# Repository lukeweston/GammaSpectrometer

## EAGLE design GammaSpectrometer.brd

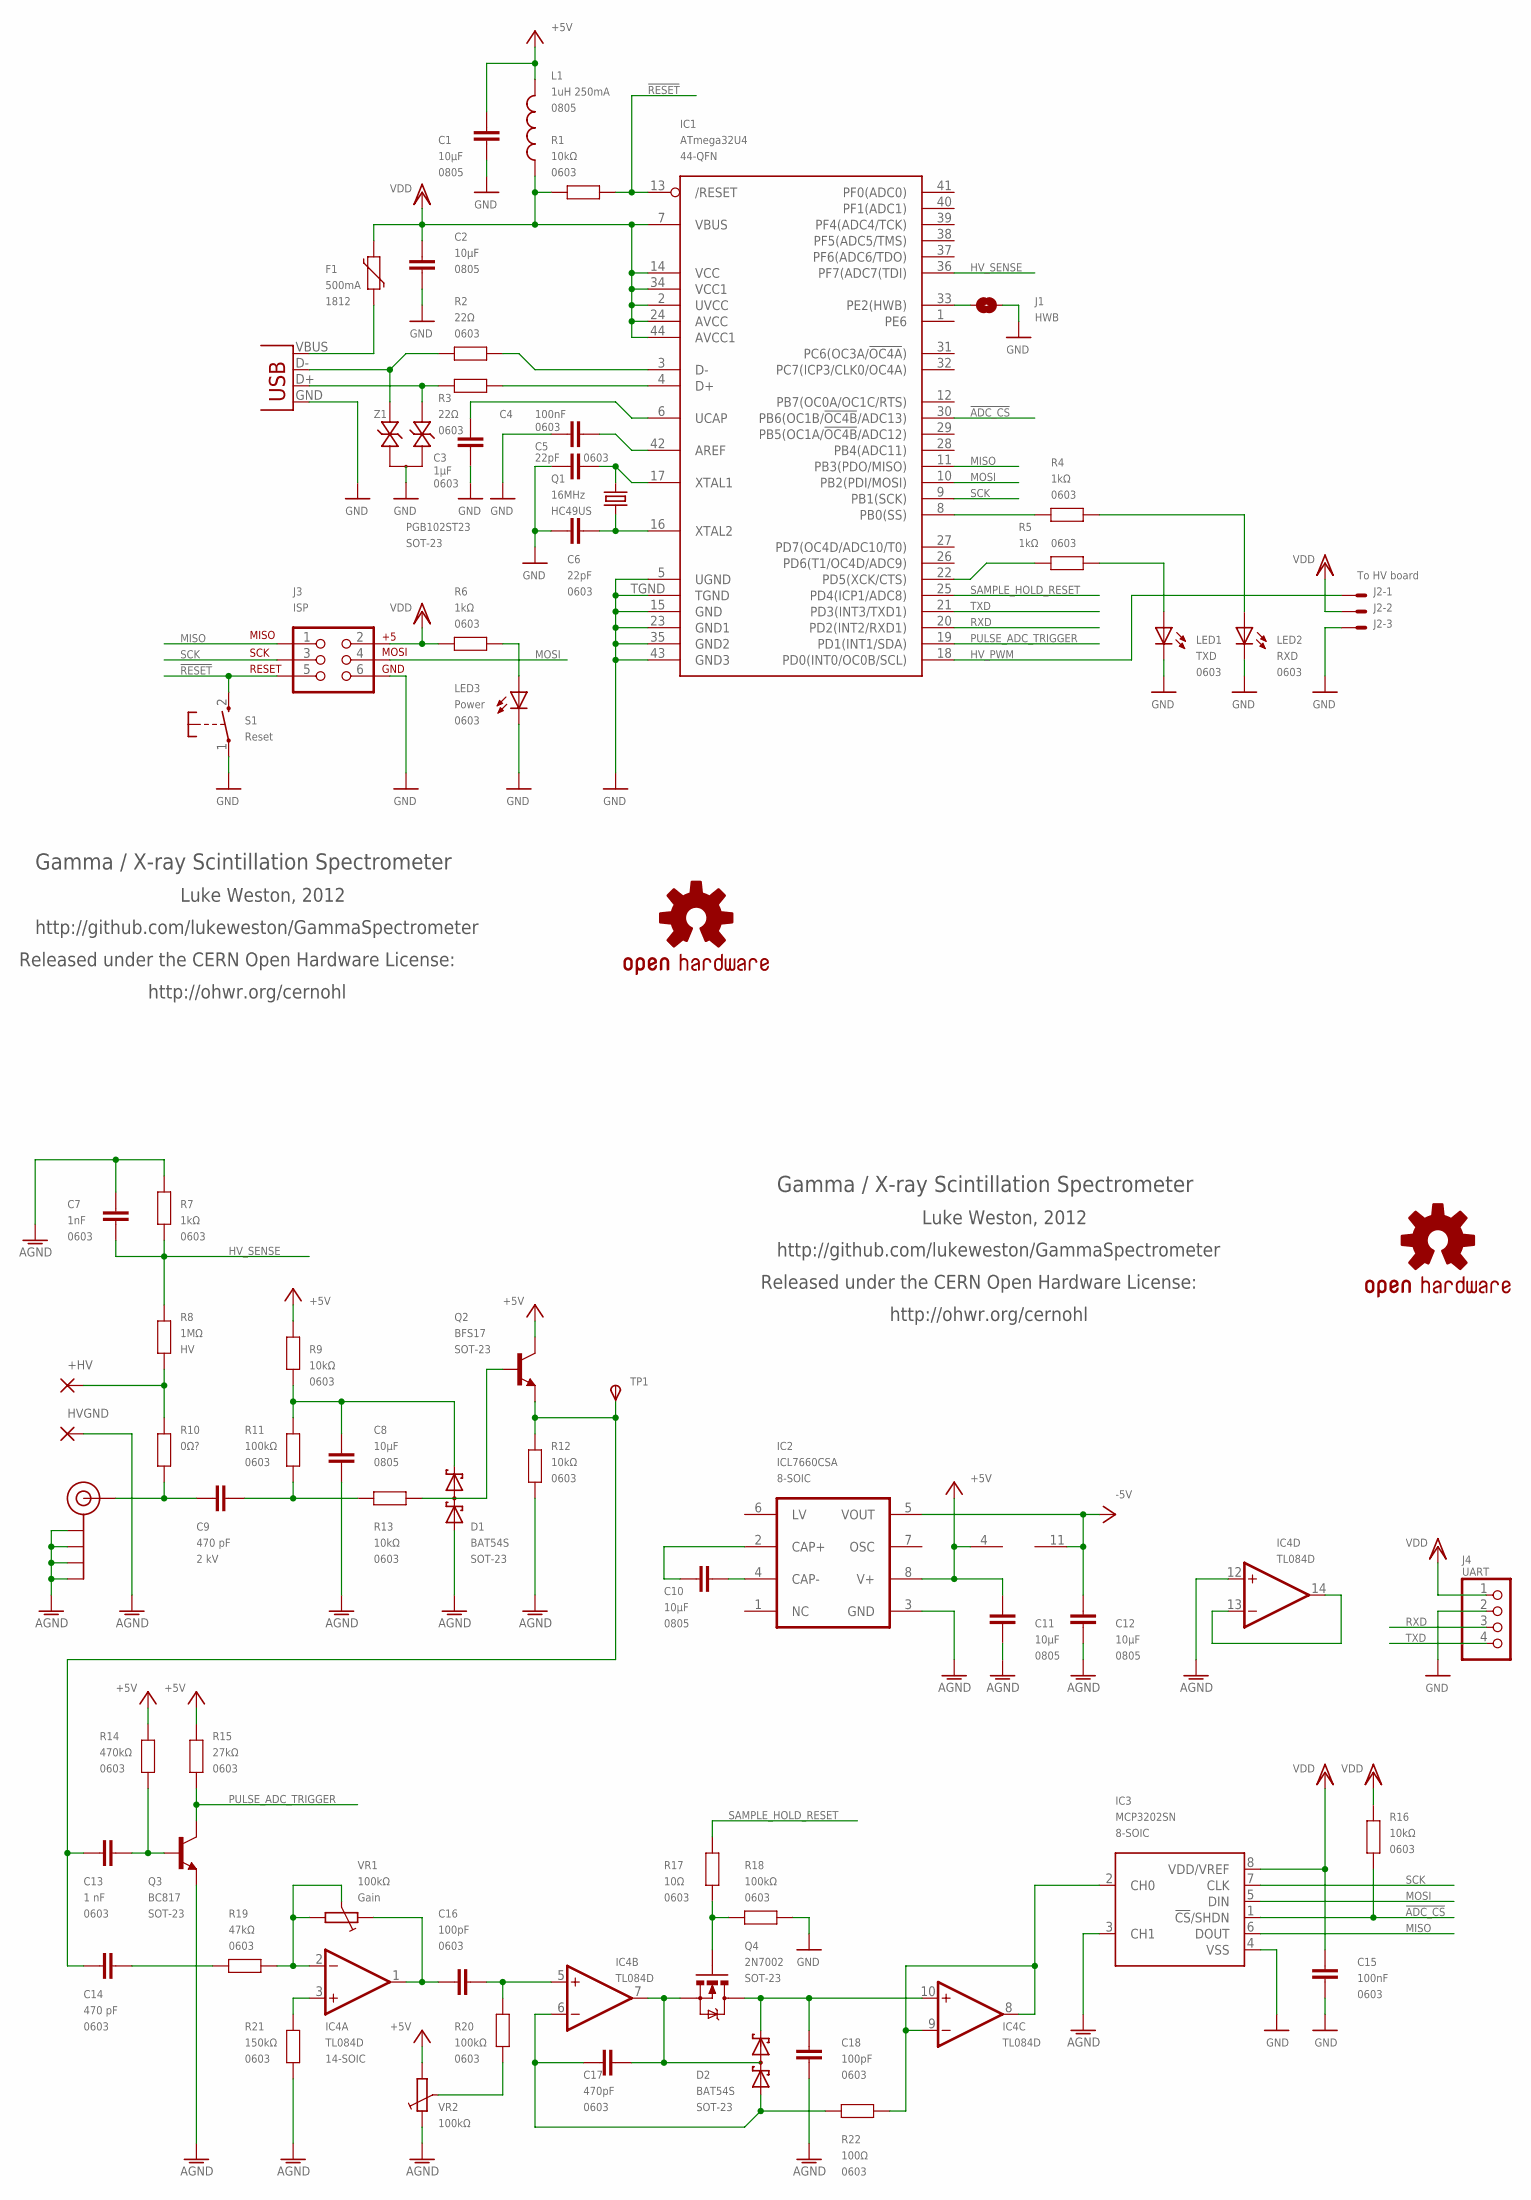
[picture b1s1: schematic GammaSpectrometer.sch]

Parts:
C1, C2, C8, C10, C11, C12: 10µF; 0805
C3: 1µF; 0603
C4, C15: 100nF; 0603
C5, C6: 22pF; 0603
C7: 1nF; 0603
C9: 470 pF; 0603; VOLTAGE 2 kV
C13: 1 nF; 0603
C14: 470 pF; 0603
C16, C18: 100pF; 0603
C17: 470pF; 0603
D1, D2: BAT54S; SOT23
F1: 500mA; 1812
IC1: ATmega32U4; QFN-44N
IC2: ICL7660CSA; SO08
IC3: MCP3202SN; SO-08
IC4: TL084D; SO14
J1: HWB; SJ
J2: To HV board; 22-23-2031
J3: ISP; 2X3-NS
J4: UART; 1X04
J$1: PMT; SMA-EDGE
L1: 1uH 250mA; L2012C
LED1: TXD; LED-0603
LED2: RXD; LED-0603
LED3: Power; LED-0603
PAD1: +HV; 2,54/0,9
PAD2: HVGND; 2,54/0,9
Q1: 16MHz; HC49US
Q2: BFS17; SOT23-BEC
Q3: BC817; SOT23-BEC
Q4: 2N7002; SOT23-3
R1, R9, R12, R13, R16: 10kΩ; 0603
R2, R3: 22Ω; 0603
R4, R5, R6, R7: 1kΩ; 0603
R8: 1MΩ; 0603; VOLTAGE HV
R10: 0Ω?; 0603
R11, R18, R20: 100kΩ; 0603
R14: 470kΩ; 0603
R15: 27kΩ; 0603
R17: 10Ω; 0603
R19: 47kΩ; 0603
R21: 150kΩ; 0603
R22: 100Ω; 0603
S1: Reset; TACTILE_SWITCH_SMD_2PIN_TINY
SY, SY1: OSHW-LOGOS; OSHW-LOGO-S
TP1: TPSPAD1-13; P1-13
VR1, VR2: 100kΩ; CT6
X1: USB-MICROB
Z1: PGB102ST23; SOT23-3

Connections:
!ADC_CS: IC1.30 (PB6(OC1B/!OC4B!/ADC13)), IC3.1 (!CS!/SHDN), R16.1
!RESET: IC1.13 (/RESET), J3.5, R1.1, S1.2 (S)
+5V: C1.1, C11.1, IC2.8 (V+), IC4.4 (V+), L1.2, Q2.C, R9.2, R14.1, R15.1, VR2.A
-5V: C12.1, IC2.5 (VOUT), IC4.11 (V-)
AGND: C7.2, C8.2, C11.2, C12.2, C18.2, D1.1 (A1), IC2.3 (GND), IC3.3 (CH1), IC4.12 (+IN), J$1.GND@0 (GND), J$1.GND@1 (GND), J$1.GND@2 (GND), J$1.GND@3 (GND), PAD2.1, Q3.E, R7.2, R12.1, R21.2, VR2.E
GND: C1.2, C2.2, C3.1, C4.1, C5.1, C6.1, C15.1, IC1.5 (UGND), IC1.15 (GND), IC1.23 (GND1), IC1.35 (GND2), IC1.43 (GND3), IC1.TGND, IC3.4 (VSS), J1.1, J2.3, J3.6, J4.2, LED1.C, LED2.C, LED3.C, R18.2, S1.1, X1.GND, Z1.3
HV_PWM: IC1.18 (PD0(INT0/OC0B/SCL)), J2.1
HV_SENSE: C7.1, IC1.36 (PF7(ADC7(TDI)), R7.1, R8.2
HWB: IC1.33 (PE2(HWB)), J1.2
MISO: IC1.11 (PB3(PDO/MISO)), IC3.6 (DOUT), J3.1
MOSI: IC1.10 (PB2(PDI/MOSI)), IC3.5 (DIN), J3.4
unnamed: PAD1.1, R8.1, R10.2
unnamed: C9.1, J$1.SIG (SIGNAL), R10.1
unnamed: C8.1, D1.3 (C2), R9.1, R11.2
unnamed: C9.2, R11.1, R13.2
unnamed: C18.1, D2.3 (C2), IC4.10 (+IN), Q4.3 (D)
unnamed: IC4.2 (-IN), R19.2, VR1.A, VR1.S
unnamed: C13.2, C14.2, Q2.E, R12.2, TP1.TP
unnamed: C14.1, R19.1
unnamed: C17.1, D2.2 (C1A2), IC4.7 (OUT), Q4.2 (S)
unnamed: IC4.3 (+IN), R21.1
unnamed: C16.2, IC4.1 (OUT), VR1.E
unnamed: D1.2 (C1A2), Q2.B, R13.1
unnamed: C13.1, Q3.B, R14.2
unnamed: R20.2, VR2.S
unnamed: C16.1, IC4.5 (+IN), R20.1
unnamed: C17.2, D2.1 (A1), IC4.6 (-IN), R22.2
unnamed: C10.2, IC2.2 (CAP+)
unnamed: C10.1, IC2.4 (CAP-)
unnamed: Q4.1 (G), R17.1, R18.1
unnamed: F1.1, X1.VBUS
unnamed: LED3.A, R6.2
unnamed: C4.2, IC1.42 (AREF)
unnamed: LED1.A, R5.2
unnamed: LED2.A, R4.2
unnamed: IC4.13 (-IN), IC4.14 (OUT)
unnamed: C3.2, IC1.6 (UCAP)
unnamed: R3.2, X1.D+, Z1.1
unnamed: R2.2, X1.D-, Z1.2
unnamed: C5.2, IC1.17 (XTAL1), Q1.2
unnamed: C6.2, IC1.16 (XTAL2), Q1.1
unnamed: IC1.4 (D+), R3.1
unnamed: IC1.3 (D-), R2.1
PULSE: IC3.2 (CH0), IC4.8 (OUT), IC4.9 (-IN), R22.1
PULSE_ADC_TRIGGER: IC1.19 (PD1(INT1/SDA)), Q3.C, R15.2
RXD: IC1.20 (PD2(INT2/RXD1)), J4.3
RXLED: IC1.8 (PB0(SS)), R4.1
SAMPLE_HOLD_RESET: IC1.25 (PD4(ICP1/ADC8)), R17.2
SCK: IC1.9 (PB1(SCK)), IC3.7 (CLK), J3.3
TXD: IC1.21 (PD3(INT3/TXD1)), J4.4
TXLED: IC1.22 (PD5(XCK/CTS)), R5.1
VDD: C2.1, C15.2, F1.2, IC1.2 (UVCC), IC1.7 (VBUS), IC1.14 (VCC), IC1.24 (AVCC), IC1.34 (VCC1), IC1.44 (AVCC1), IC3.8 (VDD/VREF), J2.2, J3.2, J4.1, L1.1, R1.2, R6.1, R16.2

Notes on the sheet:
Gamma / X-ray Scintillation Spectrometer
Luke Weston, 2012
http://github.com/lukeweston/GammaSpectrometer
Released under the CERN Open Hardware License:
http://ohwr.org/cernohl

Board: 2 copper layers, 70 parts (0 on the bottom side), 52 nets, no tracks yet.

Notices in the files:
parts and their libraries:
SparkFun-Connectors: Licensing: CC v3.0 Share-Alike You are welcome to use this library for commercial purposes.
